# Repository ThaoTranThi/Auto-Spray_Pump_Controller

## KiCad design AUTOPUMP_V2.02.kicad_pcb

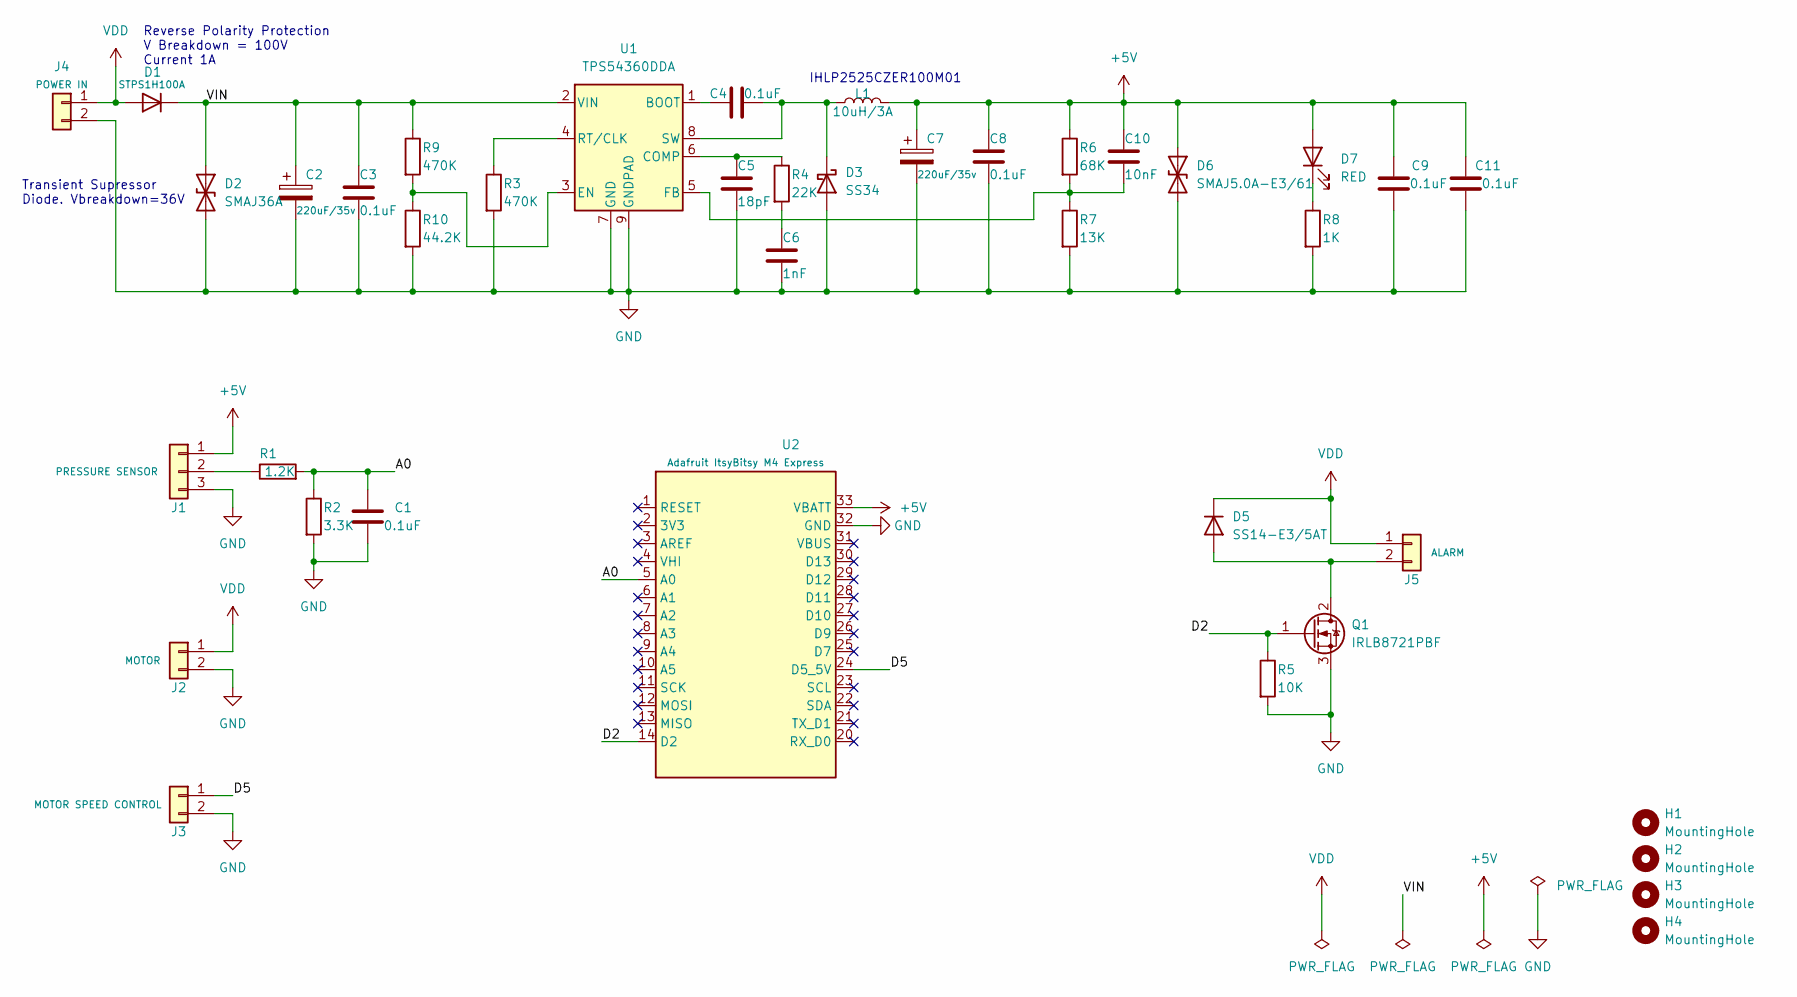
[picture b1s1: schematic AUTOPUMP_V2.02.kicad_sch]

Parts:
C1, C3, C4, C8, C9, C11: 0.1uF; C_0603_1608Metric; MPN CL10B104KB8NNWC
C2, C7: 220uF/35v; CP_Radial_D8.0mm_P3.50mm; MPN 860020574012
C5: 18pF; C_0603_1608Metric; MPN CL10C180JB81PNC
C6: 1nF; C_0603_1608Metric; MPN CL10B102KB8NFNC
C10: 10nF; C_0603_1608Metric; MPN CL10B103KB8NNWC
D1: STPS1H100A; D_SMA; MPN STPS1H100A
D2: SMAJ36A; D_SMA; MPN SMAJ36A
D3: SS34; D_SMC; MPN SS34
D5: SS14-E3/5AT; D_SMA; MPN SS14-E3/5AT
D6: SMAJ5.0A-E3/61; D_SMA; MPN SMAJ5.0A-E3/61
D7: RED; LED_0603_1608Metric; MPN LTST-C190KRKT
H1, H2, H3, H4: MountingHole; MountingHole_3.2mm_M3_standoffs; MPN 24884
J1: PRESSURE SENSOR; TerminalBlock_Phoenix_MKDS-3-3-5.08_1x03_P5.08mm_Horizontal; MPN 1711738
J2: MOTOR; TerminalBlock_Phoenix_MKDS-3-2-5.08_1x02_P5.08mm_Horizontal; MPN 1711725
J3: MOTOR SPEED CONTROL; TerminalBlock_Phoenix_MKDS-3-2-5.08_1x02_P5.08mm_Horizontal; MPN 1711725
J4: POWER IN; TerminalBlock_Phoenix_MKDS-3-2-5.08_1x02_P5.08mm_Horizontal; MPN 1711725
J5: ALARM; TerminalBlock_Phoenix_MKDS-3-2-5.08_1x02_P5.08mm_Horizontal; MPN 1711725
L1: 10uH/3A; L_Vishay_IHLP-2525; MPN IHLP2525CZER100M01
Q1: IRLB8721PBF; TO-220-3_Vertical; MPN IRLB8721PBF
R1: 1.2K; R_0603_1608Metric; MPN RMCF0603FT1K20
R2: 3.3K; R_0603_1608Metric; MPN RMCF0603FT3K30
R3, R9: 470K; R_0603_1608Metric; MPN RMCF0603FT470K
R4: 22K; R_0603_1608Metric; MPN RMCF0603FT22K0
R5: 10K; R_0603_1608Metric; MPN RNCP0603FTD10K0
R6: 68K; R_0603_1608Metric; MPN RMCF0603FT68K0
R7: 13K; R_0603_1608Metric; MPN RMCF0603FT13K0
R8: 1K; R_0603_1608Metric; MPN RNCP0603FTD1K00
R10: 44.2K; R_0603_1608Metric; MPN RMCF0603FT44K2
U1: TPS54360DDA; TI_SO-PowerPAD-8_ThermalVias; MPN TPS54360DDA
U2: Adafruit ItsyBitsy M4 Express; Adafruit-ItsyBitsy-M4; MPN nRF52840

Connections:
+5V: C7.1, C8.1, C9.2, C10.1, C11.2, D6.1 (A1), D7.2 (A), J1.1, L1.2, R6.1, U2.33 (VBATT)
/A0: C1.2, R1.2, R2.1, U2.5 (A0)
/D2: Q1.1 (G), R5.1, U2.14 (D2)
/D5: J3.1, U2.24 (D5_5V)
/VIN: C2.1, C3.1, D1.1 (K), D2.1 (A1), R9.1, U1.2 (VIN)
GND: C1.1, C2.2, C3.2, C5.2, C6.2, C7.2, C8.2, C9.1, C11.1, D2.2 (A2), D3.2 (A), D6.2 (A2), J1.3, J2.2, J3.2, J4.2, Q1.3 (S), R2.2, R3.2, R5.2, R7.2, R8.2, R10.2, U1.7 (GND), U1.9 (GNDPAD), U2.32 (GND)
unnamed: C4.1, U1.1 (BOOT)
unnamed: C4.2, D3.1 (K), L1.1, U1.8 (SW)
unnamed: C5.1, R4.1, U1.6 (COMP)
unnamed: C6.1, R4.2
unnamed: C10.2, R6.2, R7.1, U1.5 (FB)
unnamed: D5.2 (A), J5.2, Q1.2 (D)
unnamed: D7.1 (K), R8.1
unnamed: J1.2, R1.1
unnamed: R3.1, U1.4 (RT/CLK)
unnamed: R9.2, R10.1, U1.3 (EN)
VDD: D1.2 (A), D5.1 (K), J2.1, J4.1, J5.1

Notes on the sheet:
IHLP2525CZER100M01
Reverse Polarity Protection V Breakdown = 100V Current 1A
Transient Supressor Diode. Vbreakdown=36V

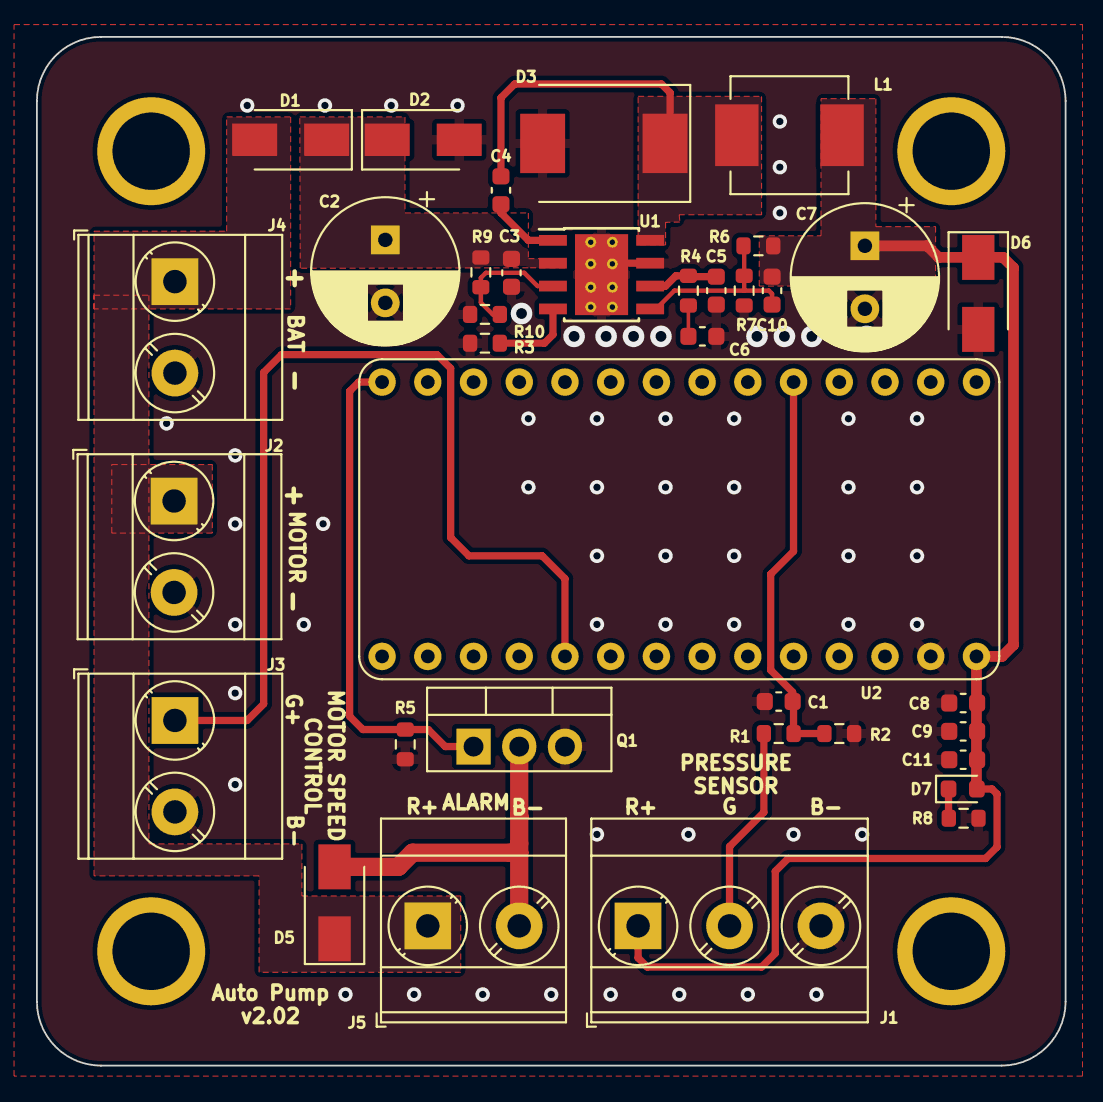
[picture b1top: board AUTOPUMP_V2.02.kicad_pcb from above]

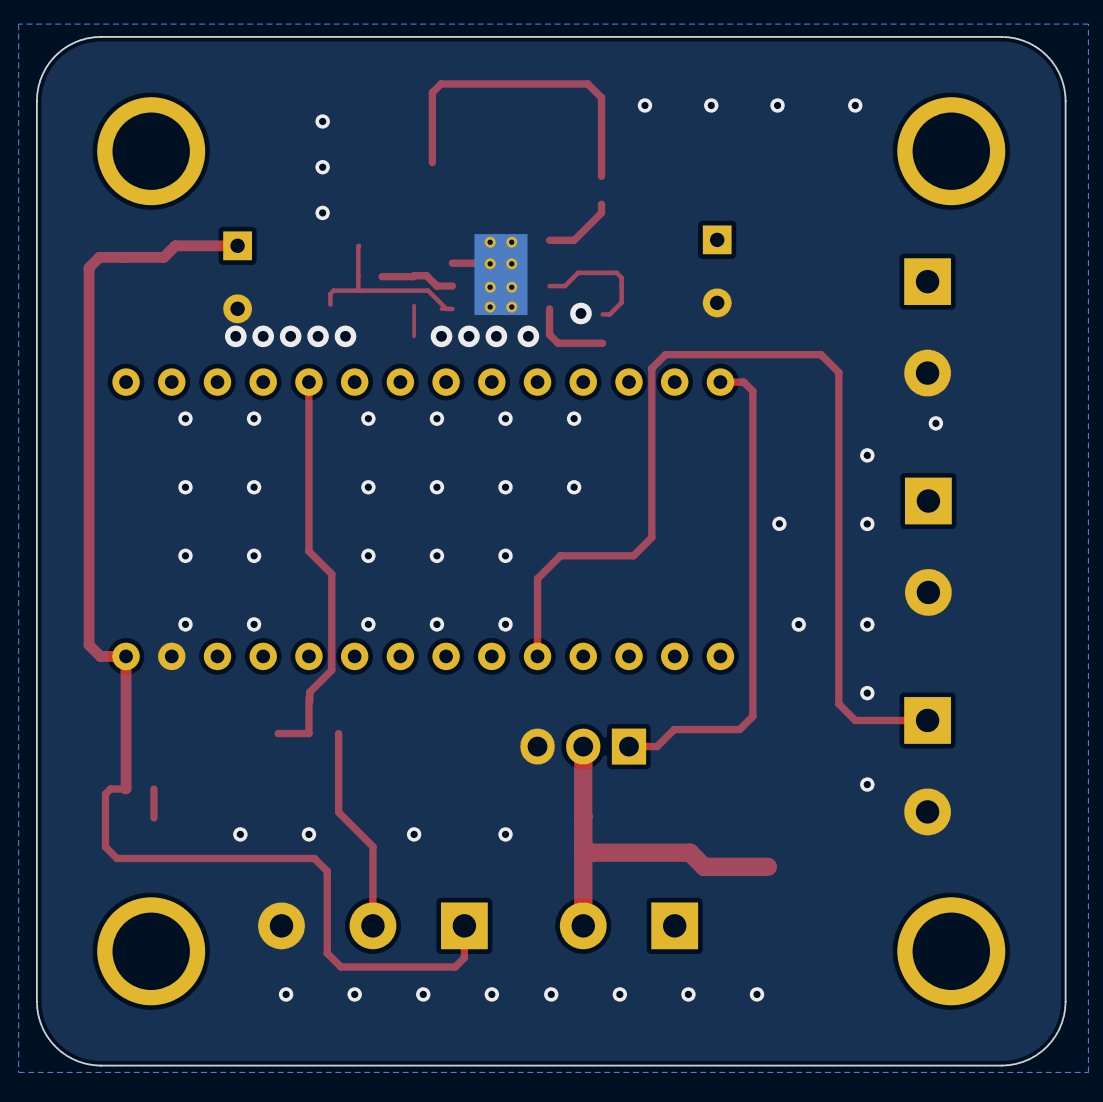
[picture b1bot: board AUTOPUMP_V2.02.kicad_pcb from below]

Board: 2 copper layers, 57.2 x 57.1 mm, 40 parts (4 on the bottom side), 17 nets.

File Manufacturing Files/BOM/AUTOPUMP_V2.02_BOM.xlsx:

BOM
Item | Qty | Designator | Value | Category | Description | MFR | MPN
1 | 6 | C1, C3, C4, C8, C9, C11 | 0.1uF | Capacitor | CAP CER 0.1UF 50V X7R 0603 | Samsung Electro-Mechanics | CL10B104KB8NNWC
2 | 2 | C2, C7 | 220uF/35v | Capacitor | CAP ALUM 220UF 20% 35V RADIAL | W眉rth Elektronik | 860020574012
3 | 1 | C5 | 18pF | Capacitor | CAP CER 18PF 50V C0G/NP0 0603 | Samsung Electro-Mechanics | CL10C180JB81PNC
4 | 1 | C6 | 1nF | Capacitor | CAP CER 1000PF 50V X7R 0603 | Samsung Electro-Mechanics | CL10B102KB8NFNC
5 | 1 | C10 | 10nF | Capacitor | CAP CER 10000PF 50V X7R 0603 | Samsung Electro-Mechanics | CL10B103KB8NNWC
6 | 1 | D1 | STPS1H100A | Diode | DIODE SCHOTTKY 100V 1A SMA | STMicroelectronics | STPS1H100A
7 | 1 | D2 | SMAJ36A | Diode | TVS DIODE 36VWM 58.1VC DO214AC | Littelfuse Inc. | SMAJ36A
8 | 1 | D3 | SS34 | Diode | DIODE SCHOTTKY 40V 3A SMC | onsemi | SS34
9 | 1 | D5 | SS14-E3/5AT | Diode | DIODE SCHOTTKY 40V 1A DO214AC | NextGen Components | SS14-E3/5AT
10 | 1 | D6 | SMAJ5.0A-E3/61 | Diode | TVS DIODE 5VWM 9.2VC DO214AC | Vishay General Semiconductor - Diodes Division | SMAJ5.0A-E3/61
11 | 1 | D7 | RED | LED | LED RED CLEAR CHIP SMD | Lite-On Inc. | LTST-C190KRKT
12 | 4 | H1, H2, H3, H4 | MountingHole | Solderrable Standoff | SM STANDOFF ON T&R 6MM | Keystone Electronics | 24884
13 | 1 | J1 | PRESSURE SENSOR | Screwed Terminal | TERM BLK 3P SIDE ENT 5.08MM PCB | Phoenix Contact | 1711738
14 | 1 | J2 | MOTOR | Screwed Terminal | TERM BLK 2P SIDE ENT 5.08MM PCB | Phoenix Contact | 1711725
15 | 1 | J3 | MOTOR SPEED CONTROL | Screwed Terminal | TERM BLK 2P SIDE ENT 5.08MM PCB | Phoenix Contact | 1711725
16 | 1 | J4 | BAT | Screwed Terminal | TERM BLK 2P SIDE ENT 5.08MM PCB | Phoenix Contact | 1711725
17 | 1 | J5 | ALARM | Screwed Terminal | TERM BLK 2P SIDE ENT 5.08MM PCB | Phoenix Contact | 1711725
18 | 1 | L1 | 10uH/3A | Power Inductor | FIXED IND 10UH 3A 105 MOHM SMD | Vishay Dale | IHLP2525CZER100M01
19 | 1 | Q1 | IRLB8721PBF | Mosfet | MOSFET N-CH 30V 62A TO220AB | Infineon Technologies | IRLB8721PBF
20 | 1 | R1 | 1.2K | Resistor | RES 1.2K OHM 1% 1/10W 0603 | Stackpole Electronics Inc | RMCF0603FT1K20
21 | 1 | R2 | 3.3K | Resistor | RES 3.3K OHM 1% 1/10W 0603 | Stackpole Electronics Inc | RMCF0603FT3K30
22 | 2 | R3, R9 | 470K | Resistor | RES 470K OHM 1% 1/10W 0603 | Stackpole Electronics Inc | RMCF0603FT470K
23 | 1 | R4 | 22K | Resistor | RES 22K OHM 1% 1/10W 0603 | Stackpole Electronics Inc | RMCF0603FT22K0
24 | 1 | R5 | 10K | Resistor | RES 10K OHM 1% 1/8W 0603 | Stackpole Electronics Inc | RNCP0603FTD10K0
25 | 1 | R6 | 68K | Resistor | RES 68K OHM 1% 1/10W 0603 | Stackpole Electronics Inc | RMCF0603FT68K0
26 | 1 | R7 | 13K | Resistor | RES 13K OHM 1% 1/10W 0603 | Stackpole Electronics Inc | RMCF0603FT13K0
27 | 1 | R8 | 1K | Resistor | RES 1K OHM 1% 1/8W 0603 | Stackpole Electronics Inc | RNCP0603FTD1K00
28 | 1 | R10 | 44.2K | Resistor | RES 44.2K OHM 1% 1/10W 0603 | Stackpole Electronics Inc | RMCF0603FT44K2
29 | 1 | U1 | TPS54360DDA | Step Down | Buck, Split Rail Switching Regulator IC Positive Adjustable 0.8V 1 Output 3.5A 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 | Texas Instruments | TPS54360DDA
30 | 1 | U2 | Adafruit ItsyBitsy M4 Express | MODULE | Adafruit ItsyBitsy M4 Express | www.adafruit.com | 3800
31 | 2 |  | 2044-1X14G00SA | CONNECTOR | PCB SOCKET, SINGLE ROW, 14 PIN, | Oupiin | 2044-1X14G00SA

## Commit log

2023-07-04 Auto Spray Pump Controller
